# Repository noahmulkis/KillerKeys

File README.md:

# KillerKeys

This is KillerKeys, A super low profile, 3dprintable, pcb based custom keyboard, using a nice!nano knockoff mc.  

## Required Parts  
(Check BOM for exact details)

- microcontroller  
- 2x pcb (pcb is reversible)  
- 1 of each required 3d printed part  
- 6x m3x8 cap head machine screws  
- switch of choice (footprints can accomadate multiple brands, I am using reddragon low profile switches)  
- 3D printed keycaps (up to personal choice of colour / design)  
- Diodes (throughhole or smd)  

## Assembly instructions

1. Solder diodes to board top.  
2. Solder headers and microcontroller to top of board.  
3. For RHS board solder together pads to reverse direction, on LHS board solder "normal" side pads together.  
4. The microcontroller headers are needed to allow the USB-C port to be accessable.  
5. Push switches through top plates.  
6. Place top plate in place, filp board upside down, and solder the switches in place.  
7. Solder Battery onto board, and place in hole in PCB.  
8. Screw bottom case in place.  
9. Flash KMK firmware.  

## Images

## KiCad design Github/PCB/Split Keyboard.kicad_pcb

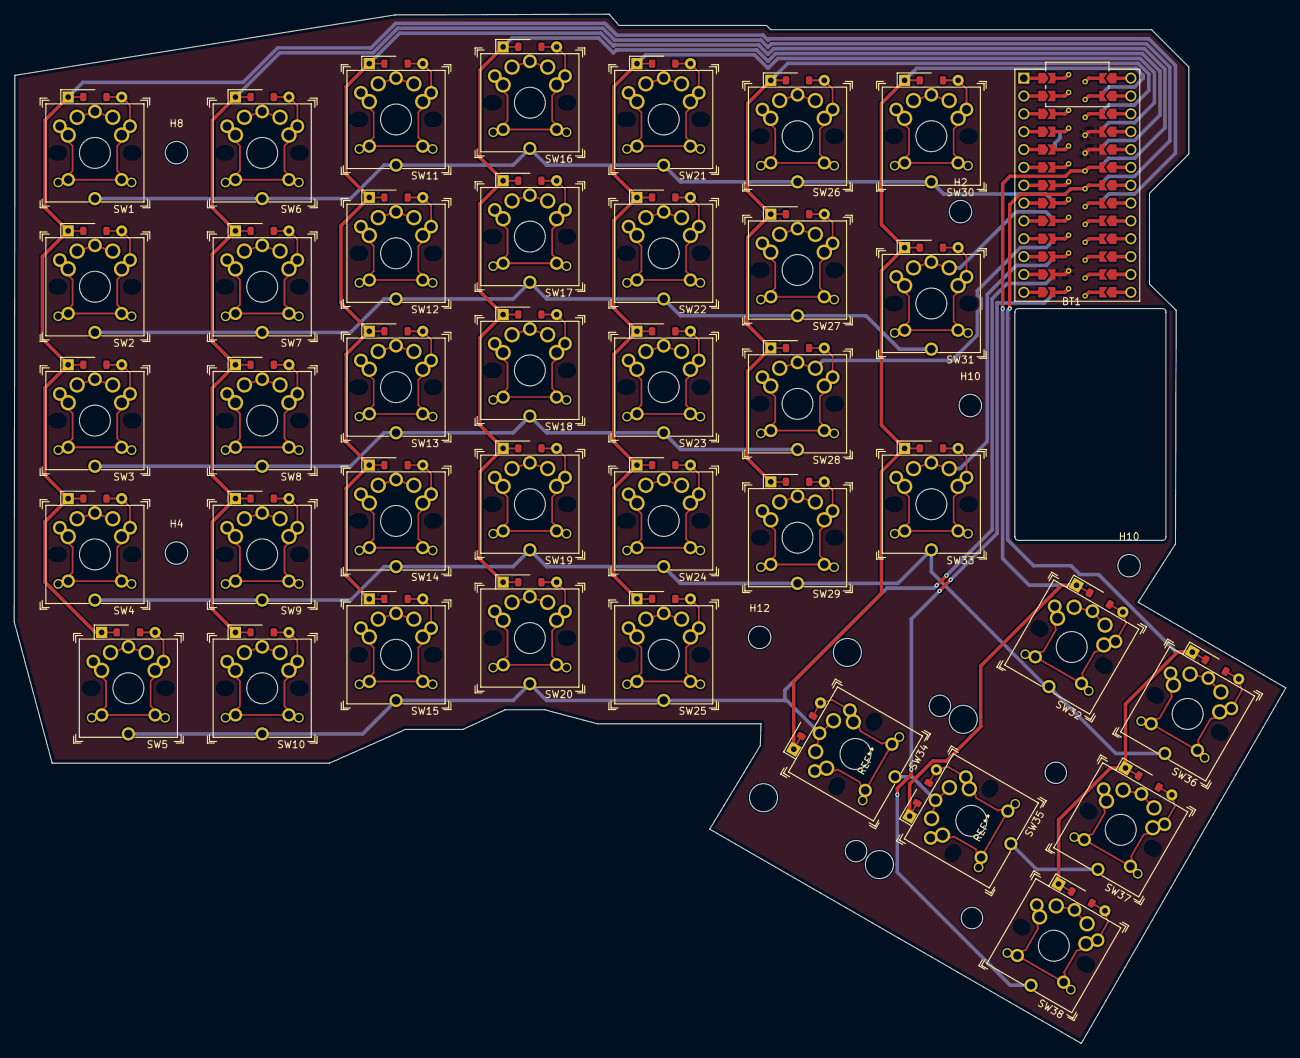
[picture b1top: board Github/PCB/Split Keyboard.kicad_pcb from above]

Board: 2 copper layers, 180.9 x 146.4 mm, 46 parts (0 on the bottom side), 16 nets.

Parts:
BT1: Battery_Cell; 503020 battery hole
H2, H4, H8, H10, H10#2, H12: MountingHole; MountingHole_3.2mm_M3
SW1, SW2, SW3, SW4, SW5, SW6, SW7, SW8, SW9, SW10, SW11, SW12, SW13, SW14, SW15, SW16, SW17, SW18, SW19, SW20, SW21, SW22, SW23, SW24, SW25, SW26, SW27, SW28, SW29, SW30, SW31, SW32, SW33, SW34, SW35, SW36, SW37, SW38: SW_UNIVERSAL_1.00u
U1: SuperMini nRF52840; ProMicro_DUAL_jumper

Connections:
COLUMN0: SW1.2, SW2.2, SW3.2, SW4.2, SW5.2, U1.18 (P0.29-LF)
COLUMN1: SW6.2, SW7.2, SW8.2, SW9.2, SW10.2, U1.19 (P0.02-LF)
COLUMN2: SW11.2, SW12.2, SW13.2, SW14.2, SW15.2, U1.20 (P1.15-LF)
COLUMN3: SW16.2, SW17.2, SW18.2, SW19.2, SW20.2, U1.21 (P1.13-LF)
COLUMN4: SW21.2, SW22.2, SW23.2, SW24.2, SW25.2, U1.22 (P1.11-LF)
COLUMN5: SW26.2, SW27.2, SW28.2, SW29.2, U1.23 (P0.10-LF)
COLUMN6: SW30.2, SW31.2, SW33.2, SW34.2, U1.24 (P0.09-LF)
COLUMN7: SW32.2, SW35.2, U1.5 (P0.17)
COLUMN8: SW36.2, SW37.2, SW38.2, U1.6 (P0.20)
GND: U1.3 (GND), U1.4 (GND), U1.14 (GND)
ROW0: SW1.1, SW6.1, SW11.1, SW16.1, SW21.1, SW26.1, SW30.1, U1.7 (P0.22)
ROW1: SW2.1, SW7.1, SW12.1, SW17.1, SW22.1, SW27.1, SW31.1, U1.8 (P0.24)
ROW2: SW3.1, SW8.1, SW13.1, SW18.1, SW23.1, SW28.1, U1.9 (P1.00)
ROW3: SW4.1, SW9.1, SW14.1, SW19.1, SW24.1, SW29.1, SW32.1, SW33.1, SW36.1, U1.10 (P0.11)
ROW4: SW5.1, SW10.1, SW15.1, SW20.1, SW25.1, SW34.1, SW35.1, SW37.1, U1.11 (P1.04-LF)
ROW5: SW38.1, U1.12 (P1.06-LF)

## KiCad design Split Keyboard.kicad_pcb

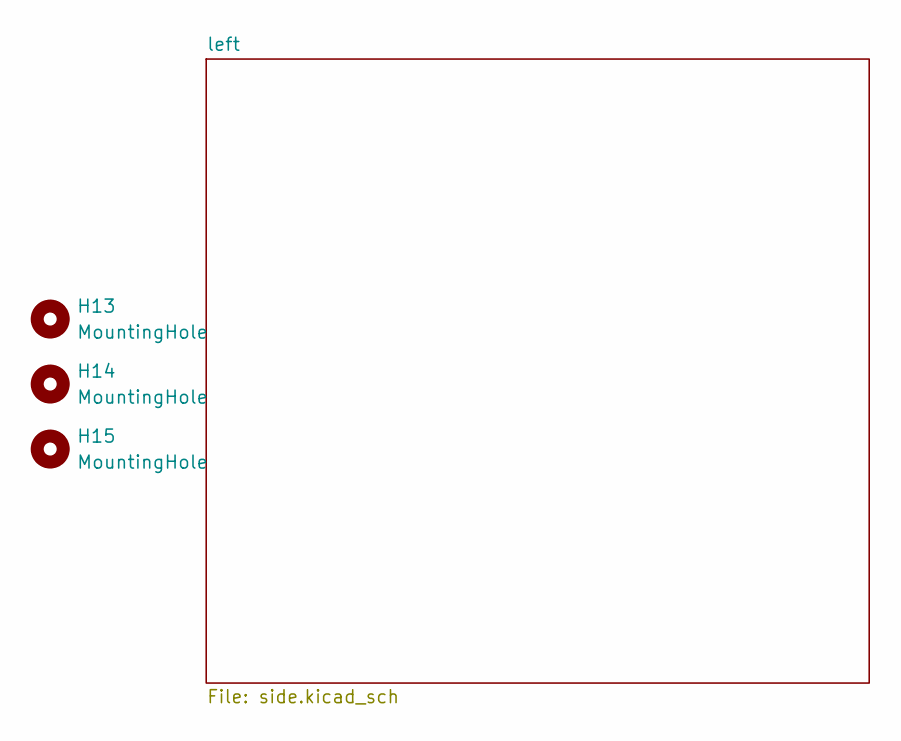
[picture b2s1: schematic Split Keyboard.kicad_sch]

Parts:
H13, H14, H15: MountingHole; MountingHole_3.2mm_M3

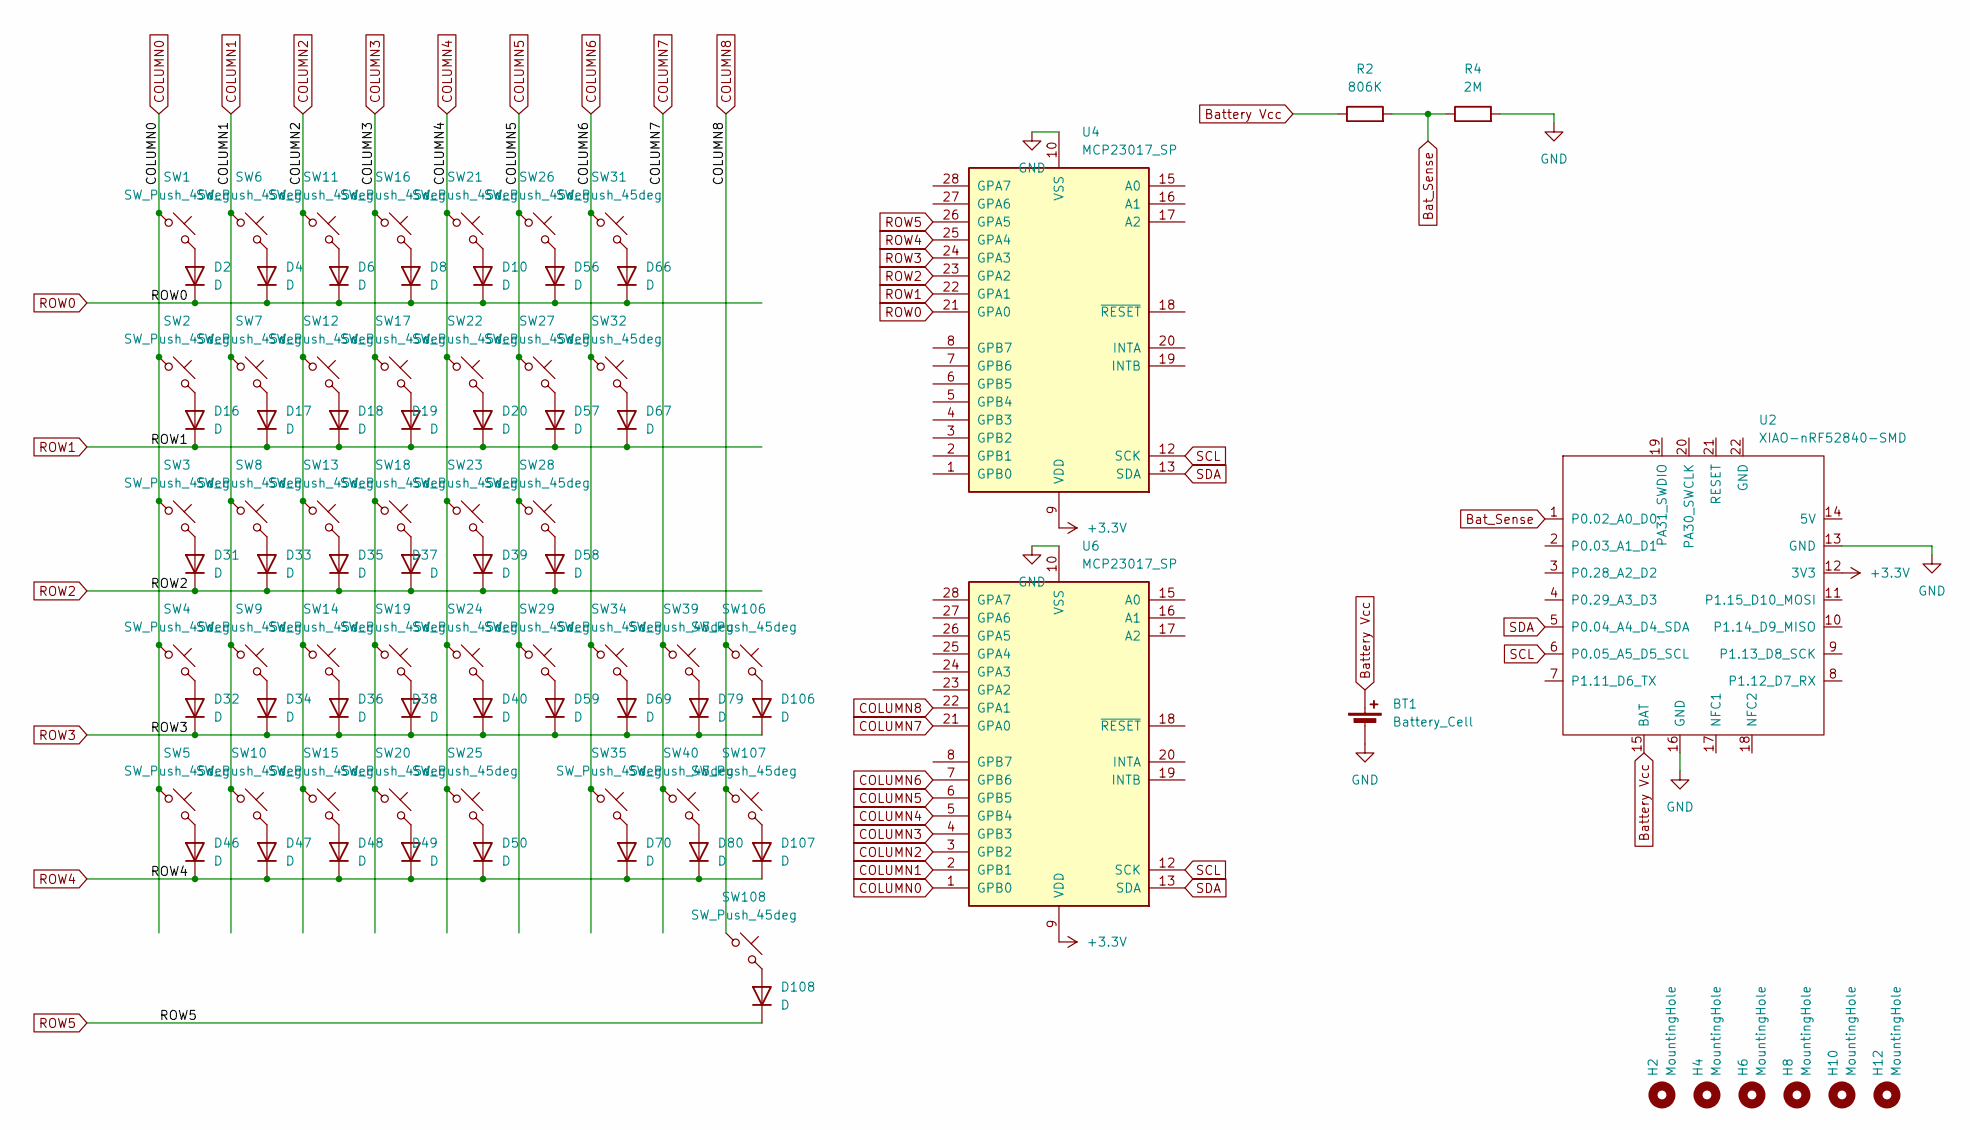
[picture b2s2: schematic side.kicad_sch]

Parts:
BT1: Battery_Cell; BatteryHolder_Keystone_1042_1x18650
D2, D4, D6, D8, D10, D16, D17, D18, D19, D20, D31, D32, D33, D34, D35, D36, D37, D38, D39, D40, D46, D47, D48, D49, D50, D56, D57, D58, D59, D66, D67, D69, D70, D79, D80, D106, D107, D108: D; D_SOD-123
H2, H4, H6, H8, H10, H12: MountingHole; MountingHole_3.2mm_M3
R2: 806K; R_0805_2012Metric
R4: 2M; R_0805_2012Metric
SW1, SW2, SW3, SW4, SW5, SW6, SW7, SW8, SW9, SW10, SW11, SW12, SW13, SW14, SW15, SW16, SW17, SW18, SW19, SW20, SW21, SW22, SW23, SW24, SW25, SW26, SW27, SW28, SW29, SW31, SW32, SW34, SW35, SW39, SW40, SW106, SW107, SW108: SW_Push_45deg; SW_Cherry_MX_1.00u_PCB
U2: XIAO-nRF52840-SMD; modified-XIAO-nRF52840-SMD
U4, U6: MCP23017_SP; DIP-28_W7.62mm

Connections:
+3.3V: U2.12 (3V3), U4.9 (VDD), U6.9 (VDD)
Bat_Sense: R2.2, R4.1, U2.1 (P0.02_A0_D0)
Battery Vcc: BT1.1 (+), R2.1, U2.15 (BAT)
COLUMN0: SW1.1, SW2.1, SW3.1, SW4.1, SW5.1, U6.1 (GPB0)
COLUMN1: SW6.1, SW7.1, SW8.1, SW9.1, SW10.1, U6.2 (GPB1)
COLUMN2: SW11.1, SW12.1, SW13.1, SW14.1, SW15.1, U6.3 (GPB2)
COLUMN3: SW16.1, SW17.1, SW18.1, SW19.1, SW20.1, U6.4 (GPB3)
COLUMN4: SW21.1, SW22.1, SW23.1, SW24.1, SW25.1, U6.5 (GPB4)
COLUMN5: SW26.1, SW27.1, SW28.1, SW29.1, U6.6 (GPB5)
COLUMN6: SW31.1, SW32.1, SW34.1, SW35.1, U6.7 (GPB6)
COLUMN7: SW39.1, SW40.1, U6.21 (GPA0)
COLUMN8: SW106.1, SW107.1, SW108.1, U6.22 (GPA1)
GND: BT1.2 (-), R4.2, U2.13 (GND), U2.16 (GND), U4.10 (VSS), U6.10 (VSS)
unnamed: D2.2 (A), SW1.2
unnamed: D4.2 (A), SW6.2
unnamed: D6.2 (A), SW11.2
unnamed: D8.2 (A), SW16.2
unnamed: D10.2 (A), SW21.2
unnamed: D16.2 (A), SW2.2
unnamed: D17.2 (A), SW7.2
unnamed: D18.2 (A), SW12.2
unnamed: D19.2 (A), SW17.2
unnamed: D20.2 (A), SW22.2
unnamed: D31.2 (A), SW3.2
unnamed: D32.2 (A), SW4.2
unnamed: D33.2 (A), SW8.2
unnamed: D34.2 (A), SW9.2
unnamed: D35.2 (A), SW13.2
unnamed: D36.2 (A), SW14.2
unnamed: D37.2 (A), SW18.2
unnamed: D38.2 (A), SW19.2
unnamed: D39.2 (A), SW23.2
unnamed: D40.2 (A), SW24.2
unnamed: D46.2 (A), SW5.2
unnamed: D47.2 (A), SW10.2
unnamed: D48.2 (A), SW15.2
unnamed: D49.2 (A), SW20.2
unnamed: D50.2 (A), SW25.2
unnamed: D56.2 (A), SW26.2
unnamed: D57.2 (A), SW27.2
unnamed: D58.2 (A), SW28.2
unnamed: D59.2 (A), SW29.2
unnamed: D66.2 (A), SW31.2
unnamed: D67.2 (A), SW32.2
unnamed: D69.2 (A), SW34.2
unnamed: D70.2 (A), SW35.2
unnamed: D79.2 (A), SW39.2
unnamed: D80.2 (A), SW40.2
unnamed: D106.2 (A), SW106.2
unnamed: D107.2 (A), SW107.2
unnamed: D108.2 (A), SW108.2
ROW0: D2.1 (K), D4.1 (K), D6.1 (K), D8.1 (K), D10.1 (K), D56.1 (K), D66.1 (K), U4.21 (GPA0)
ROW1: D16.1 (K), D17.1 (K), D18.1 (K), D19.1 (K), D20.1 (K), D57.1 (K), D67.1 (K), U4.22 (GPA1)
ROW2: D31.1 (K), D33.1 (K), D35.1 (K), D37.1 (K), D39.1 (K), D58.1 (K), U4.23 (GPA2)
ROW3: D32.1 (K), D34.1 (K), D36.1 (K), D38.1 (K), D40.1 (K), D59.1 (K), D69.1 (K), D79.1 (K), D106.1 (K), U4.24 (GPA3)
ROW4: D46.1 (K), D47.1 (K), D48.1 (K), D49.1 (K), D50.1 (K), D70.1 (K), D80.1 (K), D107.1 (K), U4.25 (GPA4)
ROW5: D108.1 (K), U4.26 (GPA5)
SCL: U2.6 (P0.05_A5_D5_SCL), U4.12 (SCK), U6.12 (SCK)
SDA: U2.5 (P0.04_A4_D4_SDA), U4.13 (SDA), U6.13 (SDA)

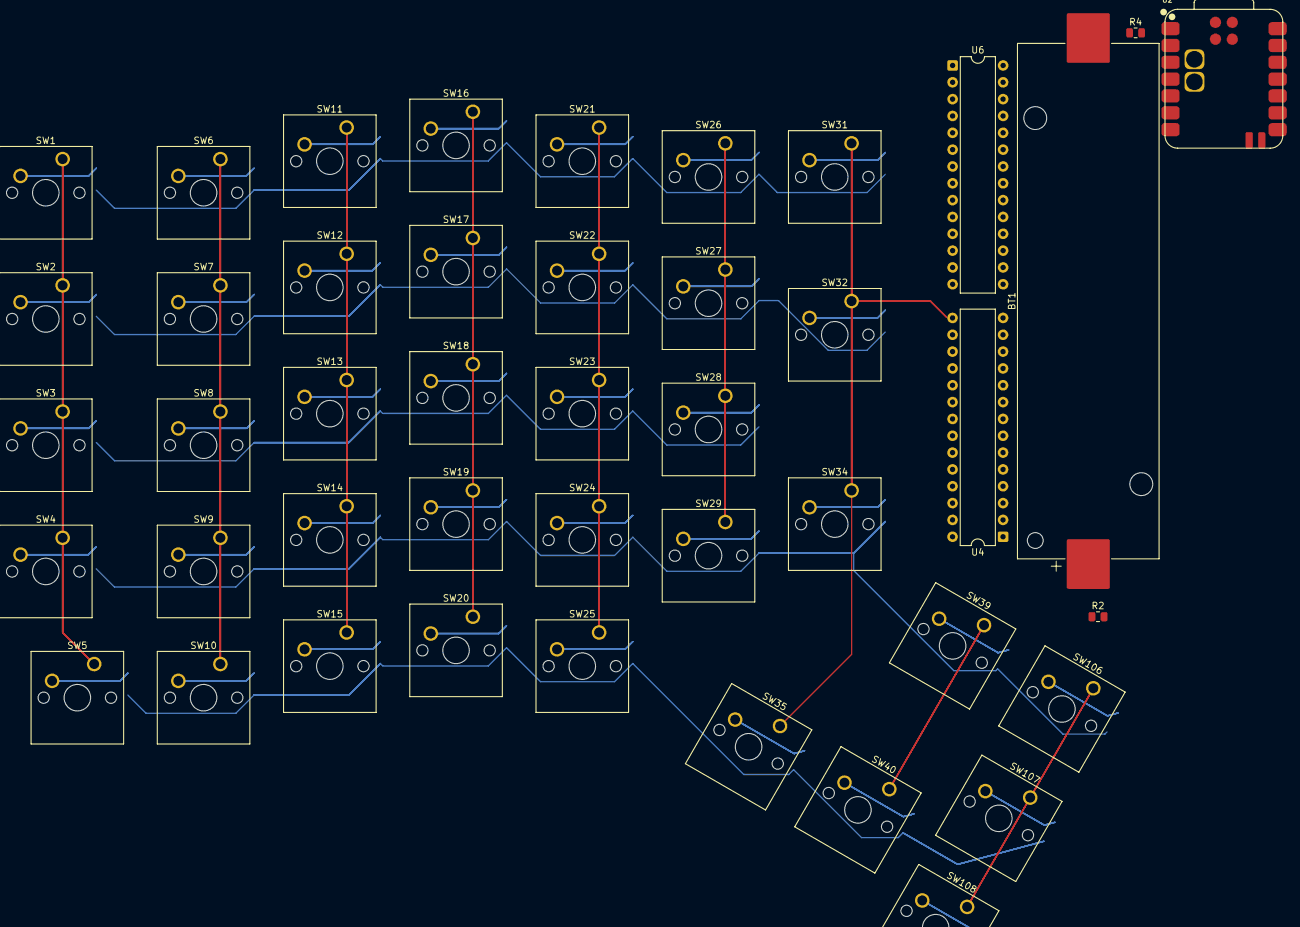
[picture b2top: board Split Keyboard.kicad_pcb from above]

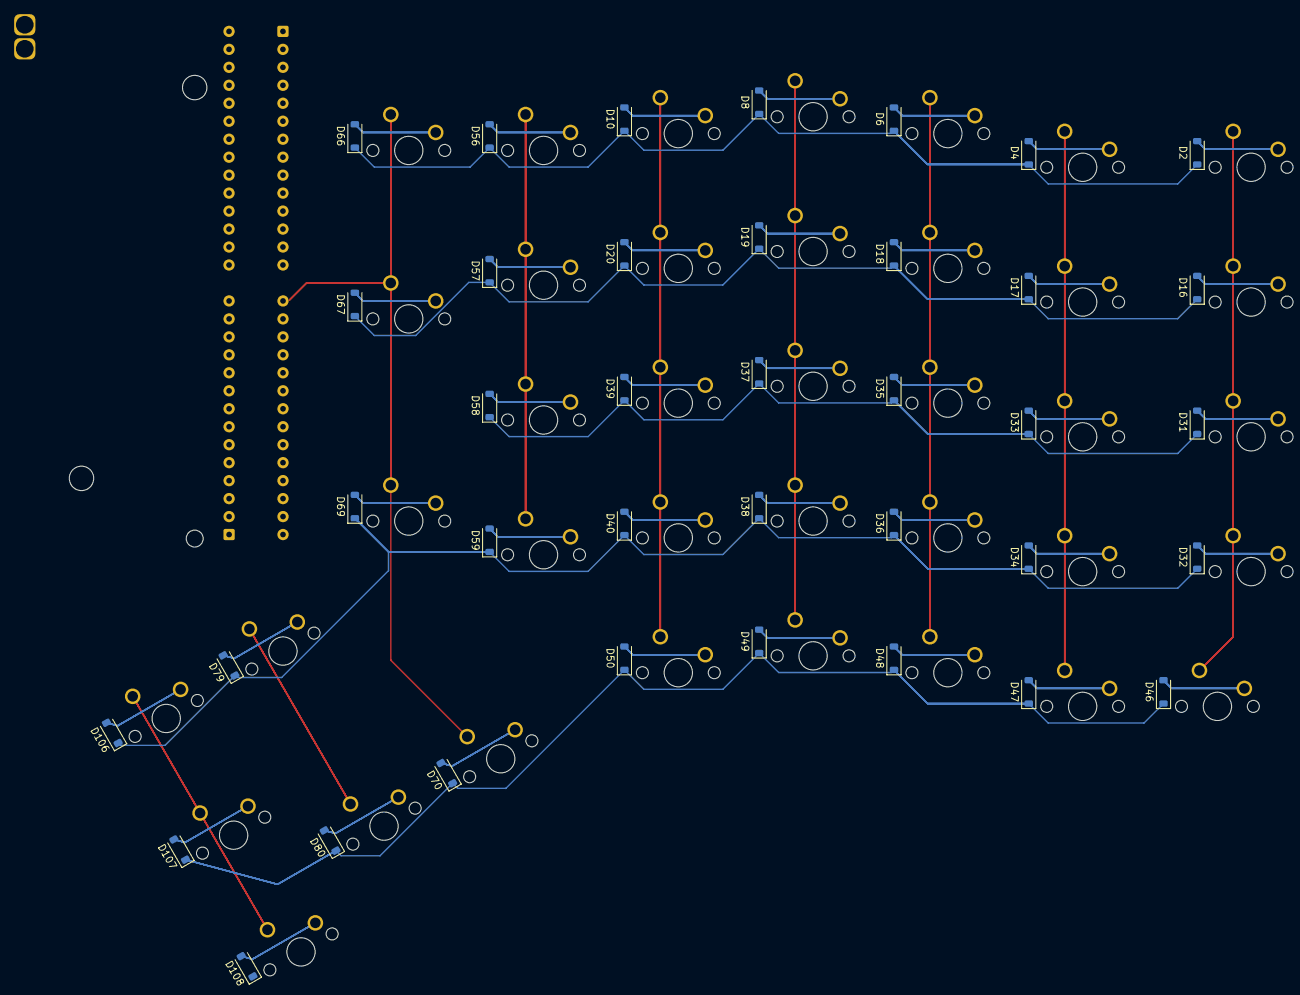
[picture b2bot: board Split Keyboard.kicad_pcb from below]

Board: 2 copper layers, 91 parts (38 on the bottom side), 59 nets.

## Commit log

2026-02-07 Add README for KillerKeys project
    Added detailed description of the KillerKeys project, including required parts, assembly instructions, and images.
